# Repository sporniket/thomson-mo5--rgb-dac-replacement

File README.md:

# Color DAC remake for the Thomson MO5 computer

> [WARNING] Please read carefully this note before using this project. It contains important facts.

Content

1. What is **Color DAC remake for the Thomson MO5 computer**, and when to use it ?
2. What should you know before using **Color DAC remake for the Thomson MO5 computer** ?
3. How to use **Color DAC remake for the Thomson MO5 computer** ?
4. Known issues
5. Miscellanous

## 1. What is **Color DAC remake for the Thomson MO5 computer**, and when to use it ?

**Color DAC remake for the Thomson MO5 computer** is a Digital to Analog Converter to translate color component levels to video voltage levels suitable for TV sets for the Thomson MO5 computer.

> The Thomson MO5 was a computer released in France in 1985.

### Licence

**Color DAC remake for the Thomson MO5 computer** is published under the Creative Commons CC0 license. You can find a copy of the licence there : https://creativecommons.org/publicdomain/zero/1.0/legalcode

You can copy, modify, distribute and perform the work, even for commercial purposes, all without asking permission.

**Color DAC remake for the Thomson MO5 computer** is distributed in the hope that it will be useful, but WITHOUT ANY WARRANTY; without even the implied warranty of MERCHANTABILITY or FITNESS FOR A PARTICULAR PURPOSE.

### Release notes

#### v1.0.0

Initial release.

## 2. What should you know before using **Color DAC remake for the Thomson MO5 computer** ?

**Color DAC remake for the Thomson MO5 computer** is made using Kicad.

> Do not use **Color DAC remake for the Thomson MO5 computer** if this project is not suitable for your project.

### Bill Of Material

|Designator(s)|Value|
|---|---|
|C1|0.1uF|
|Q1, Q2, Q3|2N3904|
|R1, R5, R9|1K5|
|R2, R6, R10|3K|
|R3, R7, R11|6K2|
|R4, R8, R12|12K|
|R13, R14, R15|1K|
|R16, R17, R18|2K|
|R19, R20, R21|150|
|R22, R23, R24|75|
|U1|74HC32|
|J1|1×9 pin header, right-angle|
|J2|1×3 pin receptacle, right-angle|

## 3. How to use **Color DAC remake for the Thomson MO5 computer** ?

### From sources

To get the latest available work, one must clone the git repository, build and install the package.

```
git clone https://github.com/sporniket/thomson-mo5--rgb-dac-replacement.git
```

Then, open the project with Kicad.

## 4. Known issues
See the [project issues](https://github.com/sporniket/thomson-mo5--rgb-dac-replacement/issues) page.

## 5. Miscellanous

### Report issues
Use the [project issues](https://github.com/sporniket/thomson-mo5--rgb-dac-replacement/issues) page.

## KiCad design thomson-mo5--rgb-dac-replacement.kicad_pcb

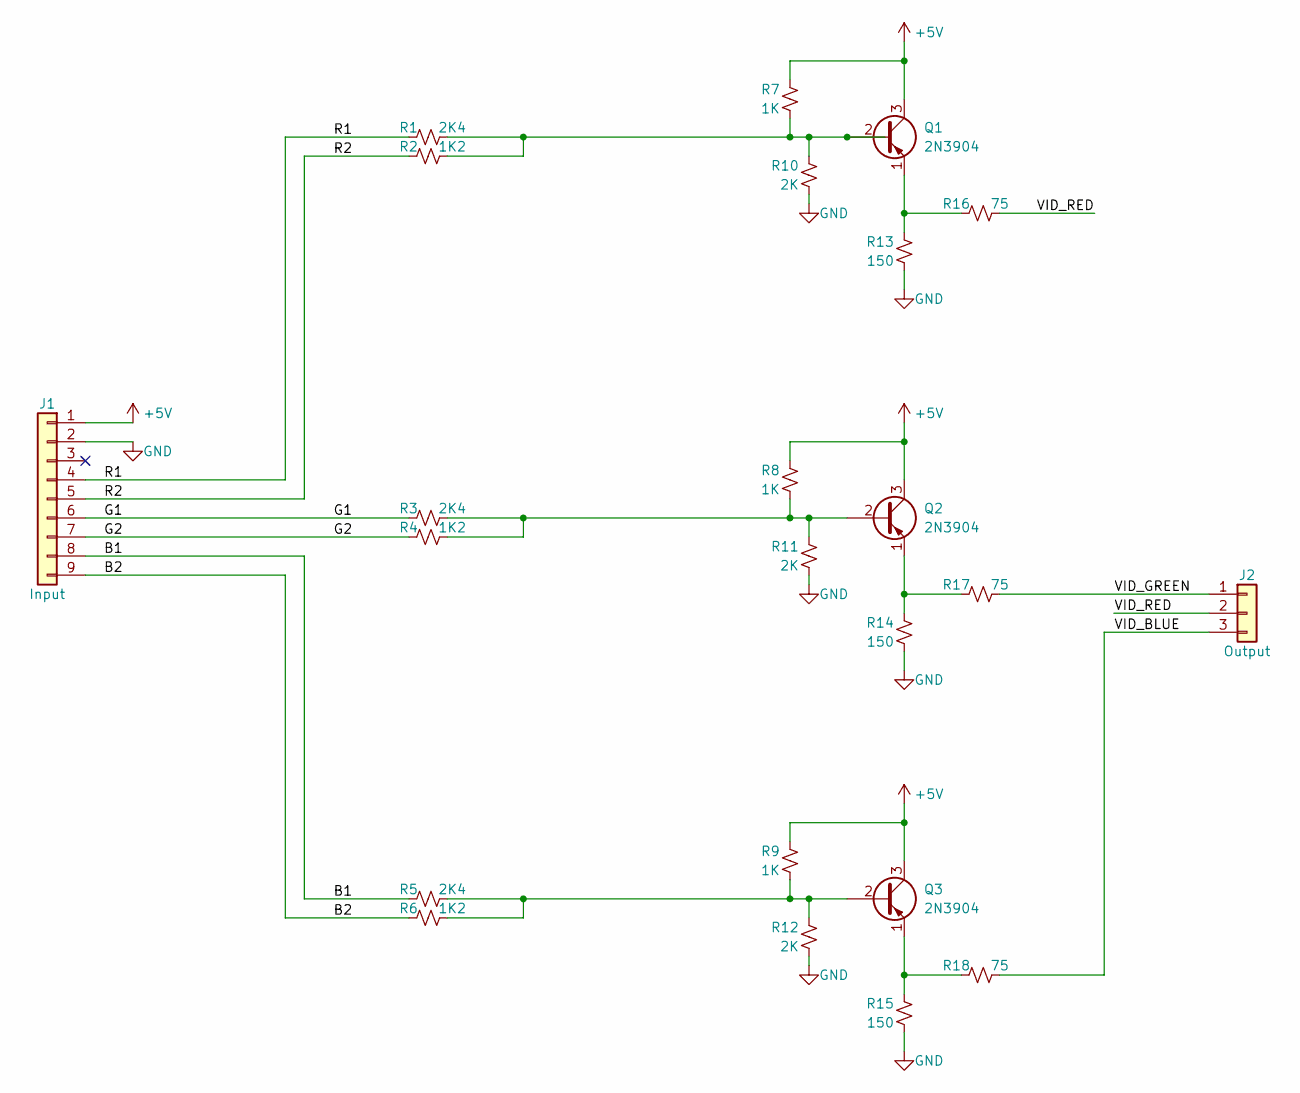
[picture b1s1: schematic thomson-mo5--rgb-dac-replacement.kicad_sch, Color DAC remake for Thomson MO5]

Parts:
J1: Input; PinHeader_1x09_P2.54mm_Vertical
J2: Output; PinHeader_1x03_P2.54mm_Vertical
Q1, Q2, Q3: 2N3904; TO-92_Inline_Wide
R1, R3, R5: 2K4; Passive_THT_resistor_W2.54mm_L12.70mm
R2, R4, R6: 1K2; Passive_THT_resistor_W2.54mm_L12.70mm
R7, R8, R9: 1K; Passive_THT_resistor_W2.54mm_L12.70mm
R10, R11, R12: 2K; Passive_THT_resistor_W2.54mm_L12.70mm
R13, R14, R15: 150; Passive_THT_resistor_W2.54mm_L12.70mm
R16, R17, R18: 75; Passive_THT_resistor_W2.54mm_L12.70mm

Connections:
+5V: J1.1, Q1.3 (C), Q2.3 (C), Q3.3 (C), R7.2, R8.2, R9.2
/B1: J1.8, R5.1
/B2: J1.9, R6.1
/G1: J1.6, R3.1
/G2: J1.7, R4.1
/R1: J1.4, R1.1
/R2: J1.5, R2.1
/VID_BLUE: J2.3, R18.2
/VID_GREEN: J2.1, R17.2
/VID_RED: J2.2, R16.2
GND: J1.2, R10.1, R11.1, R12.1, R13.1, R14.1, R15.1
unnamed: Q1.2 (B), R1.2, R2.2, R7.1, R10.2
unnamed: Q1.1 (E), R13.2, R16.1
unnamed: Q2.2 (B), R3.2, R4.2, R8.1, R11.2
unnamed: Q2.1 (E), R14.2, R17.1
unnamed: Q3.2 (B), R5.2, R6.2, R9.1, R12.2
unnamed: Q3.1 (E), R15.2, R18.1

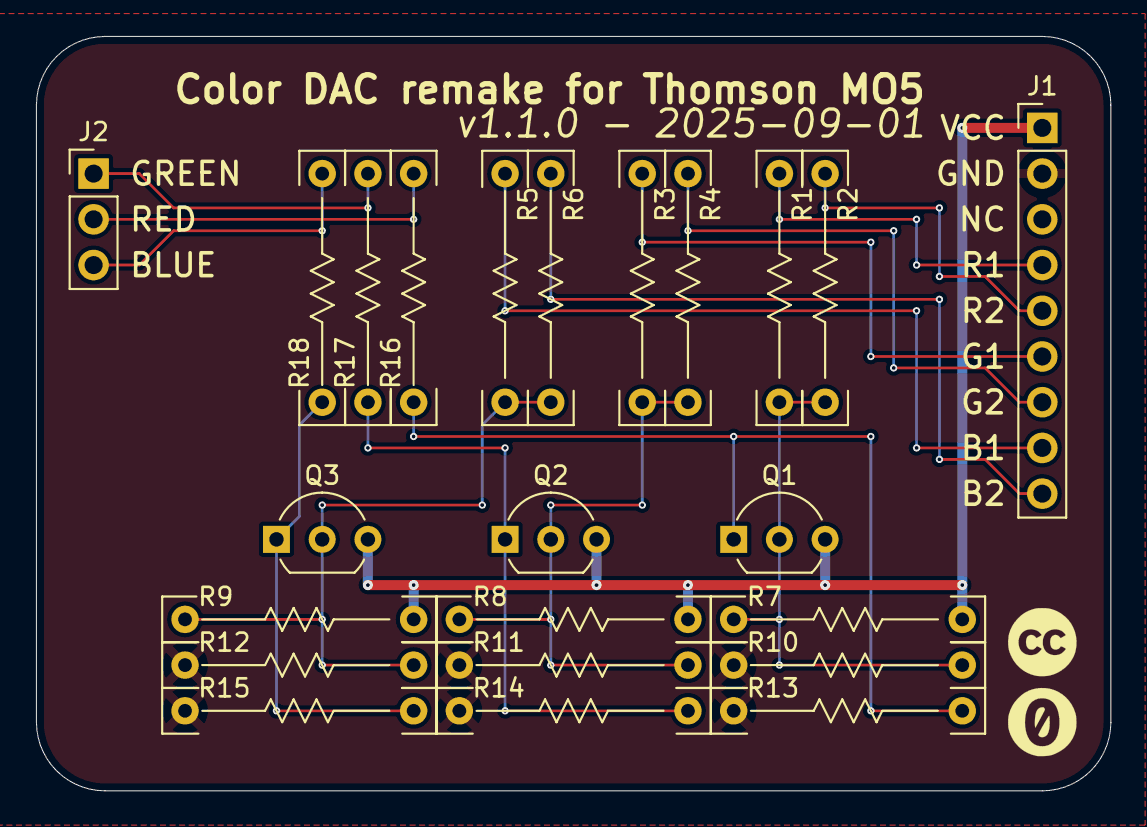
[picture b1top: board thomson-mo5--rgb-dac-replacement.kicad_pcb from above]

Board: 2 copper layers, 59.7 x 41.9 mm, 23 parts (0 on the bottom side), 17 nets.

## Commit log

2025-07-28 Initialise README
2025-07-28 Creating project files
2025-07-28 Done schematis
2025-07-28 Done PCB
2025-07-28 Added decoupling capacitor
2025-07-30 finalized pcb
2025-07-31 Final tunings in layout (schematic and pcb)
2025-07-31 prepare next release
2025-08-26 Added BOM in README
2025-09-01 Resolves #1 : [schematic] Simplify the conversion
2025-09-01 [pcb] applied schematic change, and shrinked the required size
2025-09-01 [schematic] bumped version, issue date
